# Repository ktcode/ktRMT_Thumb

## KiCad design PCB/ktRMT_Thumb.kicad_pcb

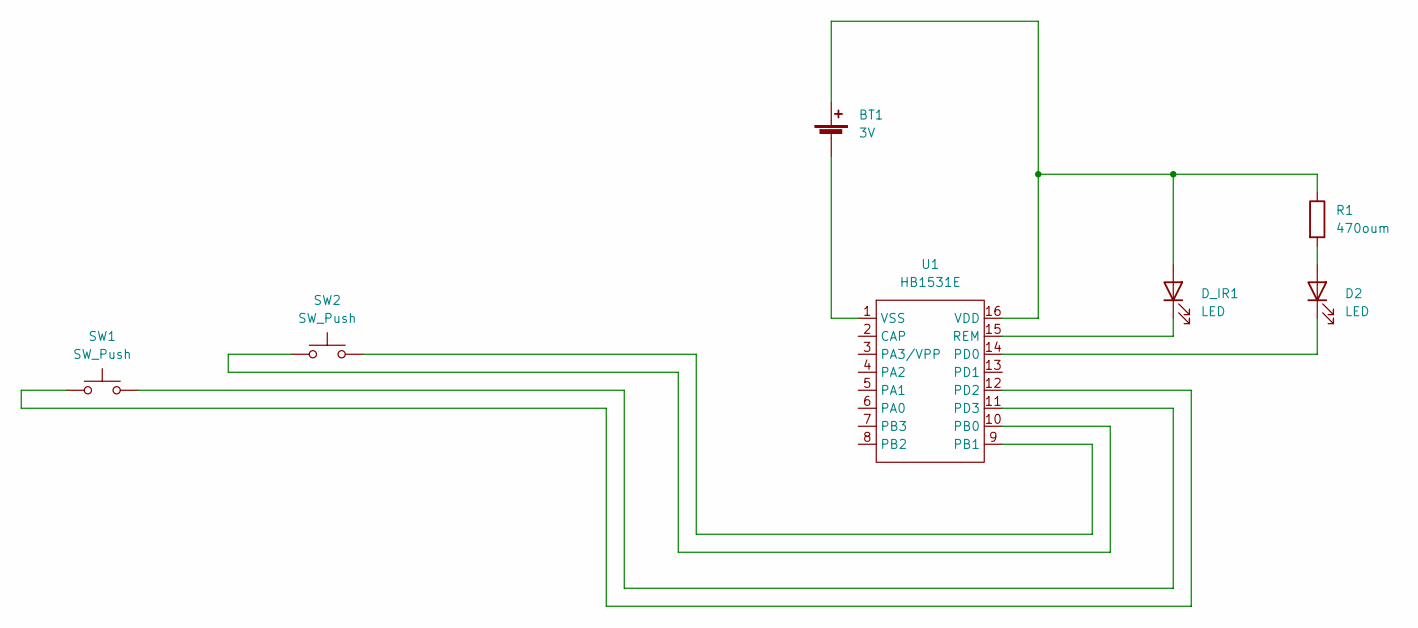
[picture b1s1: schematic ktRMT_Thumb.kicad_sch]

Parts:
BT1: 3V; CR16xx_Holder
D2: LED; LED_1206_3216Metric
D_IR1: LED; LED_D5.0mm
R1: 470oum; R_1206_3216Metric
SW1, SW2: SW_Push; MX_Socket
U1: HB1531E; SOP-16_3.9x9.9mm_P1.27mm

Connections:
unnamed: BT1.1 (+), D_IR1.2 (A), R1.1, U1.16 (VDD)
unnamed: BT1.2 (-), U1.1 (VSS)
unnamed: D2.1 (K), U1.14 (PD0)
unnamed: D2.2 (A), R1.2
unnamed: D_IR1.1 (K), U1.15 (REM)
unnamed: SW1.1, U1.12 (PD2)
unnamed: SW2.2, U1.9 (PB1)
unnamed: SW2.1, U1.10 (PB0)
unnamed: SW1.2, U1.11 (PD3)

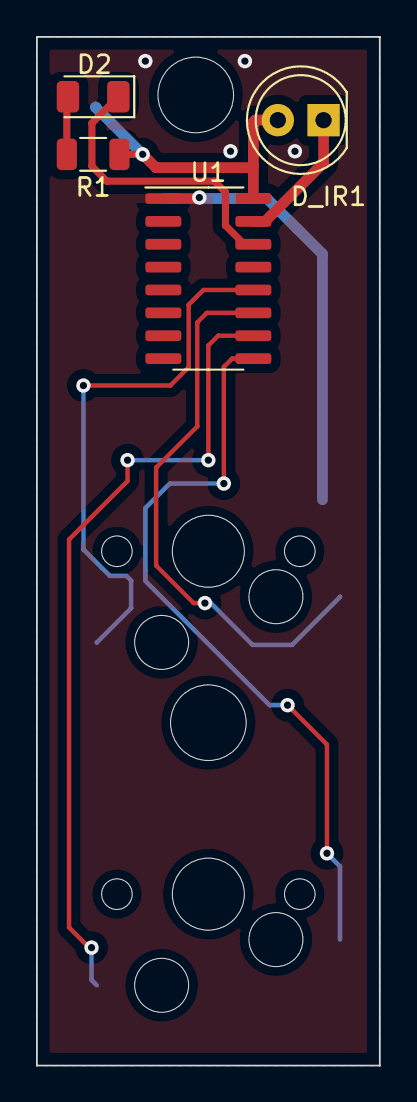
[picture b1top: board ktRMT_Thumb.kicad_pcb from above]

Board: 2 copper layers, 19.1 x 57.1 mm, 7 parts (0 on the bottom side), 9 nets.

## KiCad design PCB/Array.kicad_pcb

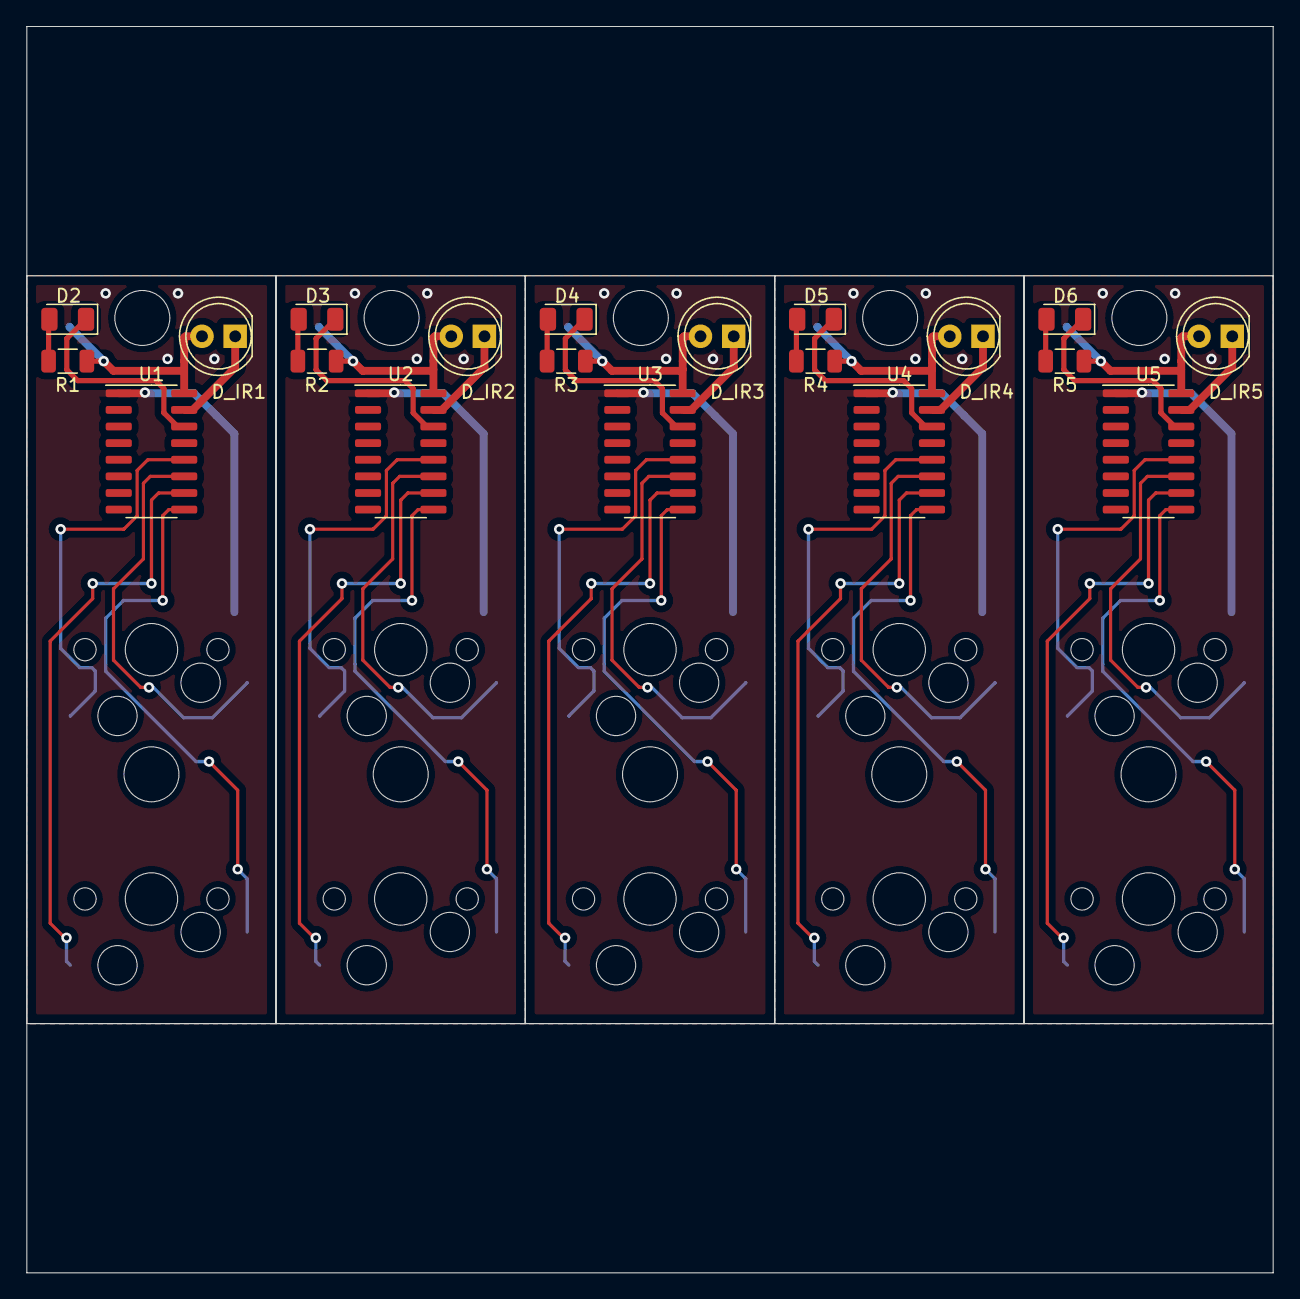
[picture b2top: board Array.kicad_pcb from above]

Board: 2 copper layers, 95.2 x 95.2 mm, 35 parts (0 on the bottom side), 9 nets.

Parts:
BT1, BT2, BT3, BT4, BT5: 3V; CR16xx_Holder
D2, D3, D4, D5, D6: LED; LED_1206_3216Metric
D_IR1, D_IR2, D_IR3, D_IR4, D_IR5: LED; LED_D5.0mm
R1, R2, R3, R4, R5: 470oum; R_1206_3216Metric
SW1, SW2, SW3, SW4, SW5, SW6, SW7, SW8, SW9, SW10: SW_Push; MX_Socket
U1, U2, U3, U4, U5: HB1531E; SOP-16_3.9x9.9mm_P1.27mm

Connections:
unnamed: BT1.1 (+), BT2.1 (+), BT3.1 (+), BT4.1 (+), BT5.1 (+), D_IR1.2 (A), D_IR2.2 (A), D_IR3.2 (A), D_IR4.2 (A), D_IR5.2 (A), R1.1, R2.1, R3.1, R4.1, R5.1, U1.16 (VDD), U2.16 (VDD), U3.16 (VDD), U4.16 (VDD), U5.16 (VDD)
unnamed: BT1.2 (-), BT2.2 (-), BT3.2 (-), BT4.2 (-), BT5.2 (-), U1.1 (VSS), U2.1 (VSS), U3.1 (VSS), U4.1 (VSS), U5.1 (VSS)
unnamed: D2.1 (K), D3.1 (K), D4.1 (K), D5.1 (K), D6.1 (K), U1.14 (PD0), U2.14 (PD0), U3.14 (PD0), U4.14 (PD0), U5.14 (PD0)
unnamed: D2.2 (A), D3.2 (A), D4.2 (A), D5.2 (A), D6.2 (A), R1.2, R2.2, R3.2, R4.2, R5.2
unnamed: D_IR1.1 (K), D_IR2.1 (K), D_IR3.1 (K), D_IR4.1 (K), D_IR5.1 (K), U1.15 (REM), U2.15 (REM), U3.15 (REM), U4.15 (REM), U5.15 (REM)
unnamed: SW1.1, SW3.1, SW5.1, SW7.1, SW9.1, U1.12 (PD2), U2.12 (PD2), U3.12 (PD2), U4.12 (PD2), U5.12 (PD2)
unnamed: SW2.2, SW4.2, SW6.2, SW8.2, SW10.2, U1.9 (PB1), U2.9 (PB1), U3.9 (PB1), U4.9 (PB1), U5.9 (PB1)
unnamed: SW2.1, SW4.1, SW6.1, SW8.1, SW10.1, U1.10 (PB0), U2.10 (PB0), U3.10 (PB0), U4.10 (PB0), U5.10 (PB0)
unnamed: SW1.2, SW3.2, SW5.2, SW7.2, SW9.2, U1.11 (PD3), U2.11 (PD3), U3.11 (PD3), U4.11 (PD3), U5.11 (PD3)

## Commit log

2025-06-25 latest
2025-06-25 Organized
